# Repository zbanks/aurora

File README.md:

aurora
======

Light controllers &amp; automation networks

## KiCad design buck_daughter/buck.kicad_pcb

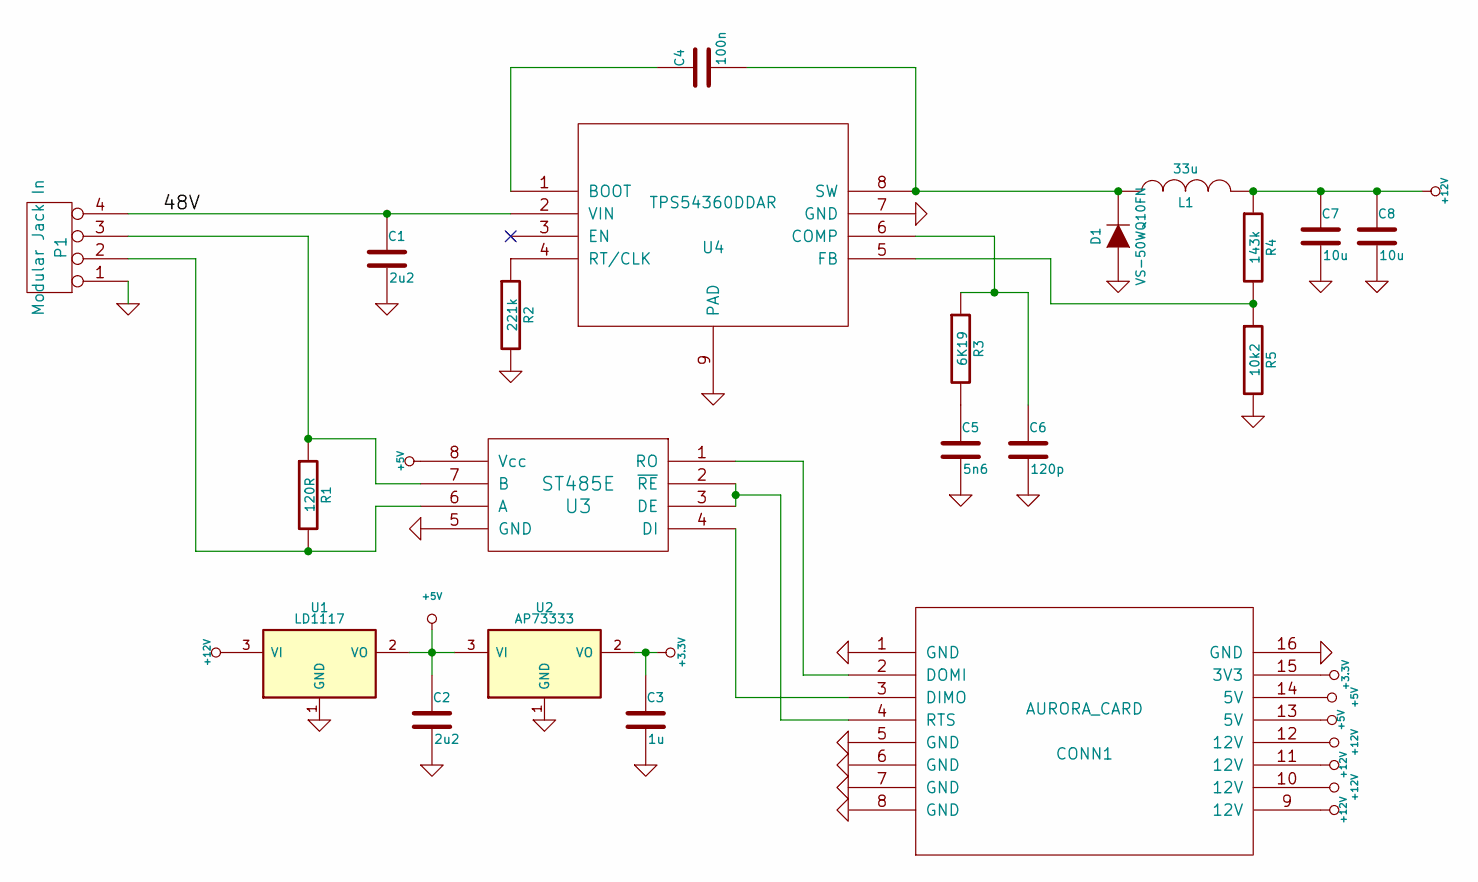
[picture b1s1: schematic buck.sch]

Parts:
C1: 2u2
C2: 2u2
C3: 1u
C4: 100n
C5: 5n6
C6: 120p
C7, C8: 10u
CONN1: AURORA_CARD; MODULE
D1: VS-50WQ10FN
L1: 33u
P1: Modular Jack In
R1: 120R
R2: 221k
R3: 6K19
R4: 143k
R5: 10k2
U1: LD1117
U2: AP73333
U3: ST485E
U4: TPS54360DDAR; MODULE

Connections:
+3.3V: C3.1, CONN1.15 (3V3), U2.2 (VO)
+5V: C2.1, CONN1.13 (5V), CONN1.14 (5V), U1.2 (VO), U2.3 (VI), U3.8 (Vcc)
+12V: C7.1, C8.1, CONN1.9 (12V), CONN1.10 (12V), CONN1.11 (12V), CONN1.12 (12V), L1.2, R4.1, U1.3 (VI)
/48V: C1.1, P1.4, U4.2 (VIN)
GND: C1.2, C2.2, C3.2, C5.2, C6.2, C7.2, C8.2, CONN1.1 (GND), CONN1.5 (GND), CONN1.6 (GND), CONN1.7 (GND), CONN1.8 (GND), CONN1.16 (GND), D1.1 (A), P1.1, R2.2, R5.2, U1.1 (GND), U2.1 (GND), U3.5 (GND), U4.7 (GND), U4.9 (PAD)
unnamed: CONN1.2 (DOMI), U3.1 (RO)
unnamed: CONN1.4 (RTS), U3.2 (~RE), U3.3 (DE)
unnamed: P1.3, R1.1, U3.7 (B)
unnamed: CONN1.3 (DIMO), U3.4 (DI)
unnamed: C5.1, R3.2
unnamed: R2.1, U4.4 (RT/CLK)
unnamed: R4.2, R5.1, U4.5 (FB)
unnamed: C6.1, R3.1, U4.6 (COMP)
unnamed: C4.1, U4.1 (BOOT)
unnamed: C4.2, D1.2 (K), L1.1, U4.8 (SW)
unnamed: P1.2, R1.2, U3.6 (A)

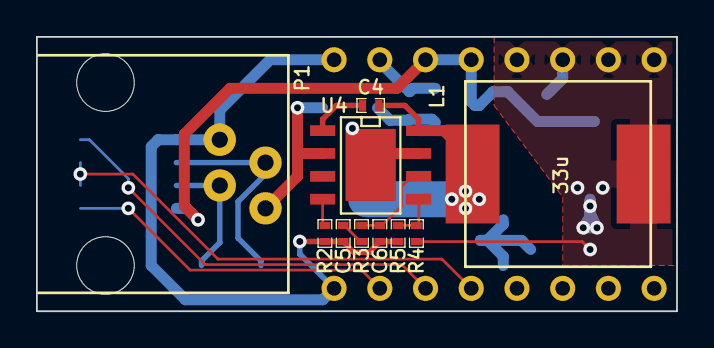
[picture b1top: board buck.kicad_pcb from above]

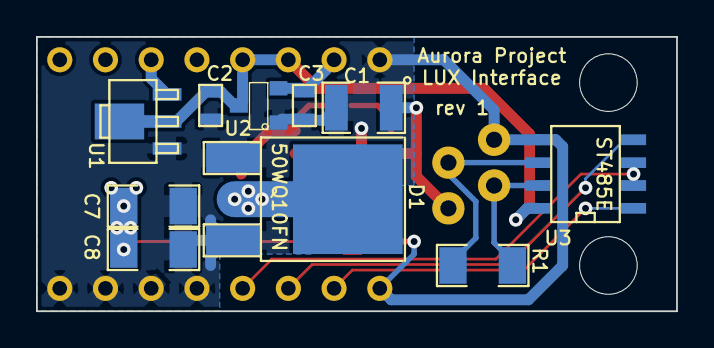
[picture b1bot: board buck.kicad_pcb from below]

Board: 2 copper layers, 35.6 x 15.2 mm, 21 parts (10 on the bottom side), 16 nets.

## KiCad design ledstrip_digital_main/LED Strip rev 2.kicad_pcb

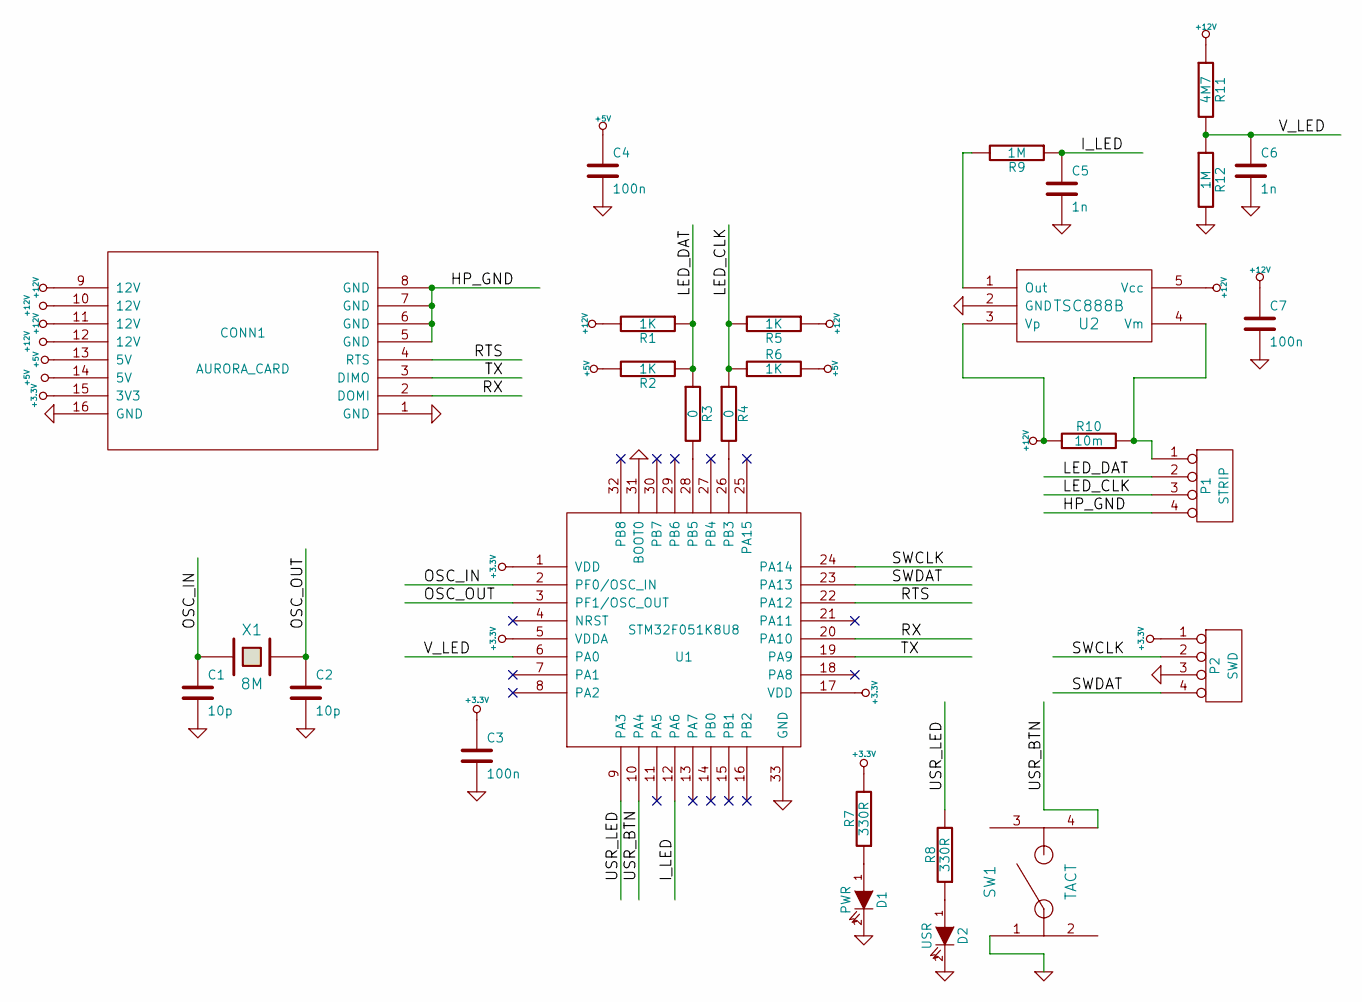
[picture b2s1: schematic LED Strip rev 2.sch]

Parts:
C1, C2: 10p
C3, C4, C7: 100n
C5, C6: 1n
CONN1: AURORA_CARD; MODULE
D1: PWR
D2: USR
P1: STRIP
P2: SWD
R1, R2, R5, R6: 1K
R3, R4: 0
R7, R8: 330R
R9, R12: 1M
R10: 10m
R11: 4M7
SW1: TACT
U1: STM32F051K8U8; MODULE
U2: TSC888B
X1: 8M

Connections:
+3.3V: C3.1, CONN1.15 (3V3), P2.1, R7.2, U1.1 (VDD), U1.5 (VDDA), U1.17 (VDD)
+5V: C4.1, CONN1.13 (5V), CONN1.14 (5V), R2.2, R6.2
+12V: C7.1, CONN1.9 (12V), CONN1.10 (12V), CONN1.11 (12V), CONN1.12 (12V), R1.2, R5.1, R10.1, R11.1, U2.3 (Vp), U2.5 (Vcc)
/HP_GND: CONN1.5 (GND), CONN1.6 (GND), CONN1.7 (GND), CONN1.8 (GND), P1.4
/I_LED: C5.1, R9.1, U1.12 (PA6)
/LED_CLK: P1.3, R4.1, R5.2, R6.1
/LED_DAT: P1.2, R1.1, R2.1, R3.1
/OSC_IN: C1.1, U1.2 (PF0/OSC_IN), X1.1
/OSC_OUT: C2.1, U1.3 (PF1/OSC_OUT), X1.2
/RTS: CONN1.4 (RTS), U1.22 (PA12)
/RX: CONN1.2 (DOMI), U1.20 (PA10)
/SWCLK: P2.2, U1.24 (PA14)
/SWDAT: P2.4, U1.23 (PA13)
/TX: CONN1.3 (DIMO), U1.19 (PA9)
/USR_BTN: SW1.4, U1.10 (PA4)
/USR_LED: R8.2, U1.9 (PA3)
/V_LED: C6.1, R11.2, R12.1, U1.6 (PA0)
GND: C1.2, C2.2, C3.2, C4.2, C5.2, C6.2, C7.2, CONN1.1 (GND), CONN1.16 (GND), D1.2 (K), D2.2 (K), P2.3, R12.2, SW1.1, U1.31 (BOOT0), U1.33 (GND), U2.2 (GND)
unnamed: R4.2, U1.26 (PB3)
unnamed: R3.2, U1.28 (PB5)
unnamed: R9.2, U2.1 (Out)
unnamed: P1.1, R10.2, U2.4 (Vm)
unnamed: D1.1 (A), R7.1
unnamed: D2.1 (A), R8.1

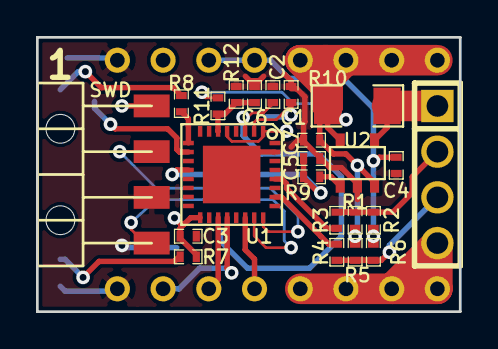
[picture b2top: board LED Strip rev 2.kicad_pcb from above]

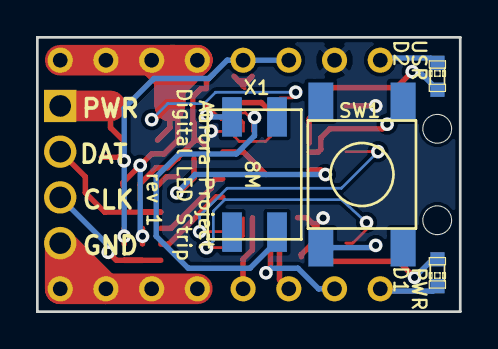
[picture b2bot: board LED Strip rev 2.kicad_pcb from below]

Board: 2 copper layers, 23.5 x 15.2 mm, 28 parts (4 on the bottom side), 24 nets.

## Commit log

2014-01-05 Adding start on digital board
2014-01-05 a little rearrangement and working on led motherboard
2014-01-05 Fixed aurora header order
2014-01-05 Changing aurora header to add another 5V pin
2014-01-05 Aurora card footprint & USB board brd
2014-01-05 Schematic for digital LED motherboard basically done
2014-01-05 Finished up schematic for digital led motherboard
2014-01-05 woo schematic
2014-01-05 Mostly routed USB card
2014-01-05 worked on part placement, almost ready to begin routing
2014-01-05 Finished usb board routing & gerbers
2014-01-06 finished copper for motherboard
2014-01-06 fixed up silkscreen + made gerbers
2014-01-06 woo buck converter copper done
2014-01-09 Finished silkscreen on daughter board, it and digital led board are done\!
2014-01-09 Tidying up zones on usb_sub
2014-01-09 removed silkscreen from outside of board
2014-01-09 panelized
2014-01-09 forgot drill files
2014-01-09 moved drl files to the right place
2014-01-09 Fixed drills on usb_sub
2014-01-13 Starting lux protocol draft
2014-01-16 Lux router
2014-01-16 Parts for the lux router
2014-01-16 Switching lux microcontroller & transciever
2014-01-16 Most of the lux router
2014-01-16 Prelimary parts assignment to lux router
2014-01-16 Board for lux router stub
2014-01-21 Routed & ordered lux router board
2014-01-24 Firmware for LED board
    HAL done
2014-01-24 housekeeping
2014-01-25 Trying to port to gnu toolchain
2014-01-25 GNU toolchain compile/flash works!
2014-01-25 DMX Device
2014-01-28 Debugging DMX
2014-01-31 Adding all of the effects that @ervanalb wanted
2014-02-07 Simple mirror
2014-07-07 Updating USB sub board
2014-07-19 Found some old files!
2014-07-23 Starting re-layout of usbsub
2014-07-23 DMX-esque + Bespeckle modes
2014-08-21 Debugging router
2014-08-22 I hate lux now
2014-08-22 Lux works!
2014-08-24 Change baud rate to 3mbps
2014-08-24 Flag select mask
2014-08-29 passive lux router
2014-09-09 relay board code
2014-09-19 Adding relay binaries
2014-09-20 add lux.py
2014-09-20 Relay control api
2014-09-20 Dummy relay control
2014-11-29 Better lux abstractions
